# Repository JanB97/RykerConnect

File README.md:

# RykerConnect
Addon Media Display for CanAm Ryker

> [!WARNING]
> Current Hardware Version (REV01) of the MainUnit has a hardware bug.
In my test, I did not connect the reset line of the display to a pin on the esp32. 
I did only connect it to the reset/enable pin of the esp. This seemed to be fine while testing, but with the production boards I am having problems with the initialization.
I would ***NOT*** recommend getting these boards produced right now.
> 
> **Update 05.04.2026**: It's fixed in software for the most part, it seems like it's working now, just a bit buggy on startup (you see weird or old images).
> I have created a Rev2 that uses a gpio as reset line, but this board is not tested, i have not ordered it and you will need to build the firmware yourseld, because you need to change the pinout from using no pin to IO15 for the display reset.

This Project contains a firmware for a esp32s3 that is build on PlattformIO and the Arduino Core, an Android Companion App to get data on the Display and a simple ESP32S3 Board design to fit within a 3D printed case.
I will publish all the projects; however, please keep in mind that I am neither a hardware designer nor a software engineer, so pretty much all of this is messy.
It works, but that is a miracle.
Originally I did intend for this to have many features (e.g., show the weather, maybe map navigation, and more), but my development skills are not good enough right now.

The current features are only:
- Display the current time
- Keep the time while turned off
- Display the current temperature (if Hardware is installed on the board)
- Display current battery percentage of the connected phone
- Display current battery percentage of the connected intercom
- Display 'Spotify' media information
- Display Youtube Music media information
- Display incoming notifications (mostly)
- Display current network status
- ota updated from github or with firmware.bin file.
- Settings for: Brightness, Batteries to show, notification display timeout
- Quick Screen Reset (in case it will still bug out with the newest firmware and only display on one side of the oled)

Things I want to add/fix:
- Notifications are currently mostly working, but sometimes apps do random things and I think the android app needs some work to handle that.

Things to add to REV3 Hardware:
- similar to REV2 extend "empty" space around and under temp sensor, to help it not warm up because of the casing and/or ESP32
- add 3 wire (V, GND, S) connector for external DS18B20 (technically possible with REV1 through the exposed pins

REV3 is most likely (if at all) the next hardware rev i am going to build, as my REV1 is working good enough now, and there is no reason to build rev2 without the external sensor now.

> [!NOTE]
> You will need Programming and Hardware knowlage to get this to work right now, I don't think I can really support this right now, so please ho ahead on your own risk.
> If you can and are willing to help with the board design and programming, feel free to help, I am glad for every help on this!

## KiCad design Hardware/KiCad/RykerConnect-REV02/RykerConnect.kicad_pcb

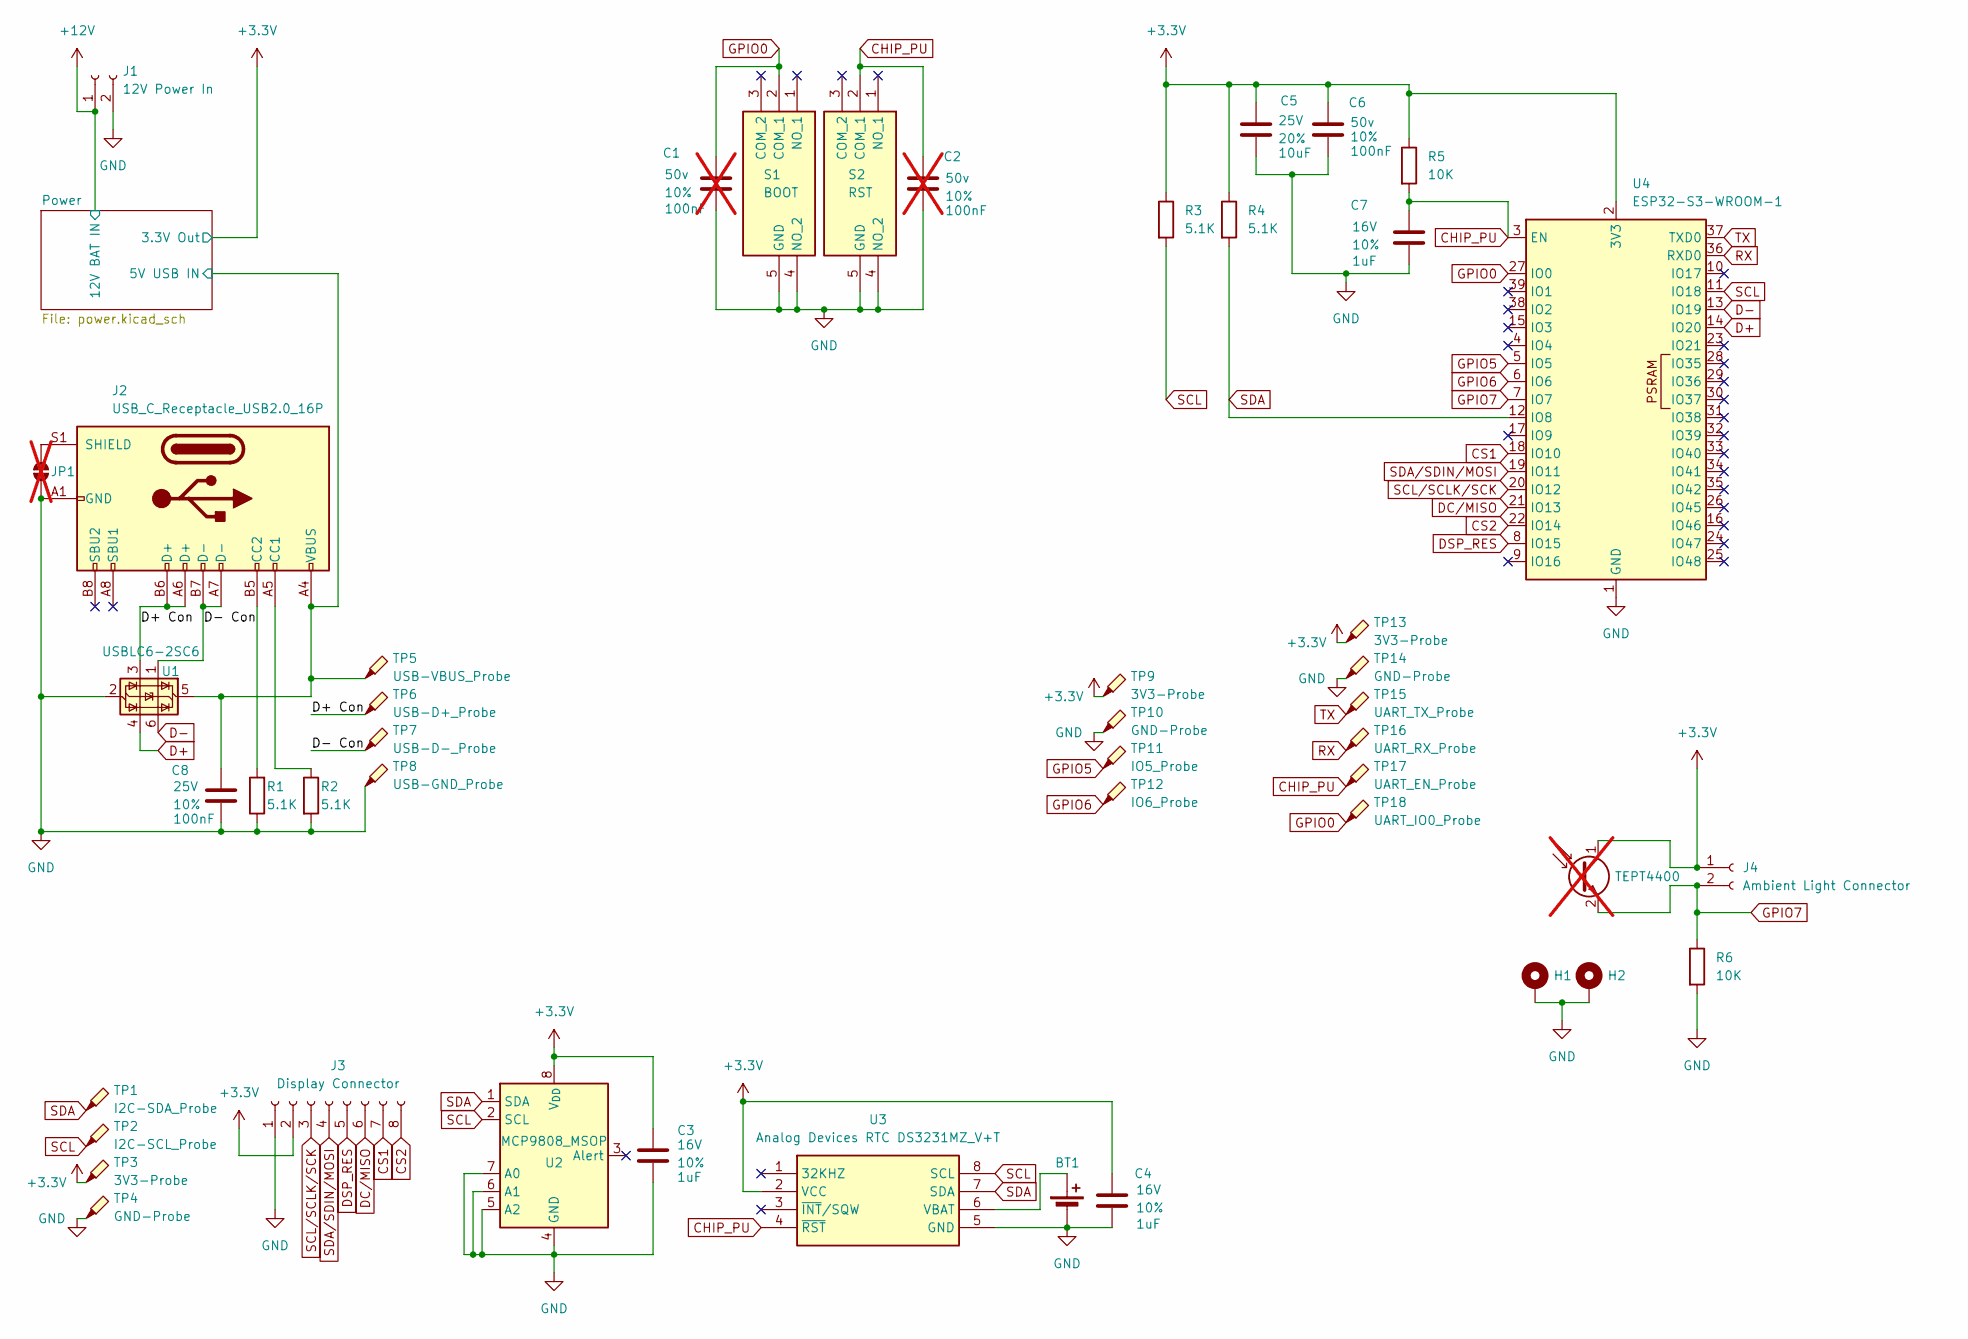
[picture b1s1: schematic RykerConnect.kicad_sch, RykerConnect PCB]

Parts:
BT1: Holders Linx CR2032; BATHLD001
C1, C2: 100nF; C_0603_1608Metric_Pad1.08x0.95mm_HandSolder; Voltage 50v; Tolerance 10%; not fitted
C3, C4, C7: 1uF; C_0603_1608Metric_Pad1.08x0.95mm_HandSolder; Voltage 16V; Tolerance 10%
C5: 10uF; C_0603_1608Metric_Pad1.08x0.95mm_HandSolder; Voltage 25V; Tolerance 20%
C6: 100nF; C_0603_1608Metric_Pad1.08x0.95mm_HandSolder; Voltage 50v; Tolerance 10%
C8: 100nF; C_0603_1608Metric_Pad1.08x0.95mm_HandSolder; Voltage 25V; Tolerance 10%
H1, H2: MountingHole_Pad; MountingHole_2.2mm_M2_ISO14580_Pad_TopBottom
J1: 12V Power In; 43650-02_00,01,02_
J2: USB_C_Receptacle_USB2.0_16P; USB_C_Receptacle_GCT_USB4105-xx-A_16P_TopMnt_Horizontal
J3: Display Connector; JST_SH_SM08B-SRSS-TB_1x08-1MP_P1.00mm_Horizontal
J4: Ambient Light Connector; JST_SH_SM02B-SRSS-TB_1x02-1MP_P1.00mm_Horizontal
JP1: SolderJumper_2_Open; R_0603_1608Metric_Pad0.98x0.95mm_HandSolder; not fitted
Q1: TEPT4400; LED_D3.0mm_Clear; not fitted
R1, R2, R3, R4: 5.1K; R_0805_2012Metric_Pad1.20x1.40mm_HandSolder
R5: 10K; R_0805_2012Metric_Pad1.20x1.40mm_HandSolder; Tolerance 1%
R6: 10K; R_0805_2012Metric_Pad1.20x1.40mm_HandSolder
S1: BOOT; 435451019820; Mouser Part Number 710-435451019820
S2: RST; 435451019820; Mouser Part Number 710-435451019820
TP1: I2C-SDA_Probe; TestPoint_Pad_D2.0mm
TP2: I2C-SCL_Probe; TestPoint_Pad_D2.0mm
TP3, TP9: 3V3-Probe; TestPoint_Pad_D2.0mm
TP4, TP10: GND-Probe; TestPoint_Pad_D2.0mm
TP5: USB-VBUS_Probe; TestPoint_Pad_D1.0mm
TP6: USB-D+_Probe; TestPoint_Pad_D1.0mm
TP7: USB-D-_Probe; TestPoint_Pad_D1.0mm
TP8: USB-GND_Probe; TestPoint_Pad_D1.0mm
TP11: IO5_Probe; TestPoint_Pad_D2.0mm
TP12: IO6_Probe; TestPoint_Pad_D2.0mm
TP13: 3V3-Probe; TestPoint_Pad_D1.5mm
TP14: GND-Probe; TestPoint_Pad_D1.5mm
TP15: UART_TX_Probe; TestPoint_Pad_D1.5mm
TP16: UART_RX_Probe; TestPoint_Pad_D1.5mm
TP17: UART_EN_Probe; TestPoint_Pad_D1.5mm
TP18: UART_IO0_Probe; TestPoint_Pad_D1.5mm
U1: USBLC6-2SC6; SOT-23-6
U2: MCP9808_MSOP; MSOP-8_3x3mm_P0.65mm
U3: Analog Devices RTC DS3231MZ_V+T; SOIC127P600X175-8N; Mouser Part Number 700-DS3231MZ/V+T
U4: ESP32-S3-WROOM-1

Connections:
+3.3V: C3.1, C4.1, C5.1, C6.1, J3.2, J4.1, Q1.1 (C), R3.1, R4.1, R5.1, TP3.1 (1_1), TP9.1 (1_1), TP13.1 (1_1), U2.8 (V_{DD}), U3.2 (VCC), U4.2 (3V3); also elsewhere on the board
+12V: J1.1; also elsewhere on the board
/D+ Con: J2.A6 (D+), J2.B6 (D+), TP6.1 (1_1), U1.3 (I/O2)
/D- Con: J2.A7 (D-), J2.B7 (D-), TP7.1 (1_1), U1.1 (I/O1)
/Power/5V USB IN: C8.1, J2.A4 (VBUS), J2.A9 (VBUS), J2.B4 (VBUS), J2.B9 (VBUS), TP5.1 (1_1), U1.5 (VBUS); also elsewhere on the board
CHIP_PU: C2.1, C7.1, R5.2, S2.2 (COM_1), TP17.1 (1_1), U3.4 (~RST), U4.3 (EN)
CS1: J3.7, U4.18 (IO10)
CS2: J3.8, U4.22 (IO14)
D+: U1.4 (I/O2), U4.14 (IO20)
D-: U1.6 (I/O1), U4.13 (IO19)
DC/MISO: J3.6, U4.21 (IO13)
DSP_RES: J3.5, U4.8 (IO15)
GND: BT1.2 (-), C1.2, C2.2, C3.2, C4.2, C5.2, C6.2, C7.2, C8.2, H1.1 (1_1), H2.1 (1_1), J1.2, J2.A1 (GND), J2.A12 (GND), J2.B1 (GND), J2.B12 (GND), J3.1, JP1.1 (A), R1.1, R2.2, R6.2, S1.4 (NO_2), S1.5 (GND), S2.4 (NO_2), S2.5 (GND), TP4.1 (1_1), TP8.1 (1_1), TP10.1 (1_1), TP14.1 (1_1), U1.2 (GND), U2.4 (GND), U2.5 (A2), U2.6 (A1), U2.7 (A0), U3.5 (GND), U4.1 (GND), U4.40 (GND), U4.41 (GND); also elsewhere on the board
GPIO0: C1.1, S1.2 (COM_1), TP18.1 (1_1), U4.27 (IO0)
GPIO5: TP11.1 (1_1), U4.5 (IO5)
GPIO6: TP12.1 (1_1), U4.6 (IO6)
GPIO7: J4.2, Q1.2 (E), R6.1, U4.7 (IO7)
unnamed: BT1.1 (+), U3.6 (VBAT)
unnamed: J2.A5 (CC1), R2.1
unnamed: J2.B5 (CC2), R1.2
unnamed: J2.S1 (SHIELD), JP1.2 (B)
RX: TP16.1 (1_1), U4.36 (RXD0)
SCL: R3.2, TP2.1 (1_1), U2.2 (SCL), U3.8 (SCL), U4.11 (IO18)
SCL/SCLK/SCK: J3.3, U4.20 (IO12)
SDA: R4.2, TP1.1 (1_1), U2.1 (SDA), U3.7 (SDA), U4.12 (IO8)
SDA/SDIN/MOSI: J3.4, U4.19 (IO11)
TX: TP15.1 (1_1), U4.37 (TXD0)

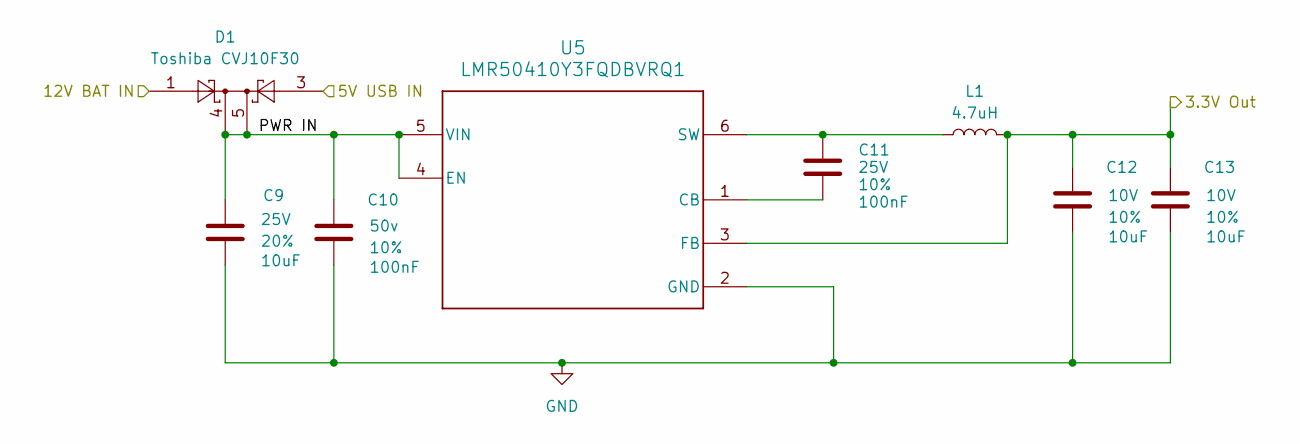
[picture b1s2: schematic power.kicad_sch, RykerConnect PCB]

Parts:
C9: 10uF; C_0603_1608Metric_Pad1.08x0.95mm_HandSolder; Voltage 25V; Tolerance 20%
C10: 100nF; C_0603_1608Metric_Pad1.08x0.95mm_HandSolder; Voltage 50v; Tolerance 10%
C11: 100nF; C_0603_1608Metric_Pad1.08x0.95mm_HandSolder; Voltage 25V; Tolerance 10%
C12, C13: 10uF; C_0805_2012Metric_Pad1.18x1.45mm_HandSolder; Voltage 10V; Tolerance 10%
D1: Toshiba CVJ10F30; SOTFL65P210X75-5N
L1: 4.7uH; INDPM5653X430N
U5: LMR50410Y3FQDBVRQ1; DBV0006A-IPC_A

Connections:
+3.3V: C12.1, C13.1, L1.2, U5.3 (FB); also elsewhere on the board
+12V: D1.1; also elsewhere on the board
/Power/5V USB IN: D1.3; also elsewhere on the board
/Power/PWR IN: C9.1, C10.1, D1.4, D1.5, U5.4 (EN), U5.5 (VIN)
GND: C9.2, C10.2, C12.2, C13.2, U5.2 (GND); also elsewhere on the board
unnamed: C11.2, U5.1 (CB)
unnamed: C11.1, L1.1, U5.6 (SW)

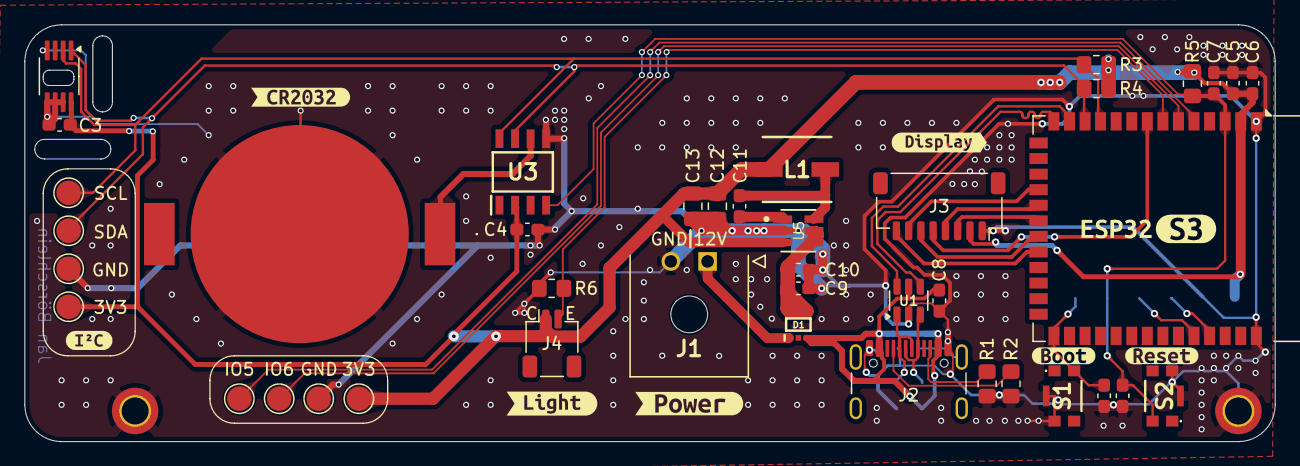
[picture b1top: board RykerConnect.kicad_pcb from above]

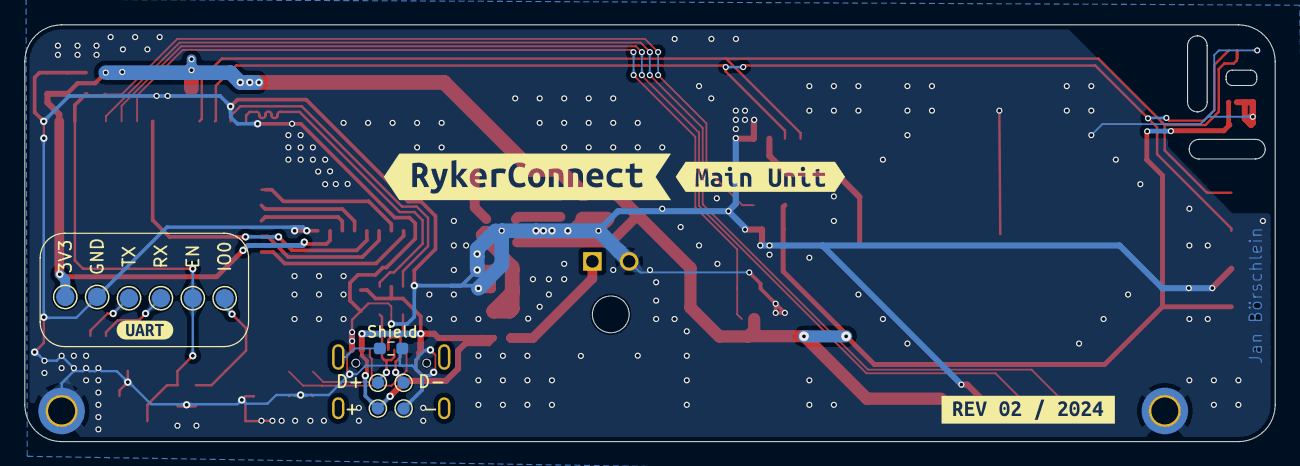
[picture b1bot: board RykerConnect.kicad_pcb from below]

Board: 2 copper layers, 102.0 x 34.0 mm, 67 parts (16 on the bottom side), 30 nets.

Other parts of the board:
kibuzzard-6647CFBD: G***; kibuzzard-6647CFBD
kibuzzard-66281C1F: G***; kibuzzard-66281C1F
kibuzzard-66281DA5: G***; kibuzzard-66281DA5
kibuzzard-66281FA1: G***; kibuzzard-66281FA1
kibuzzard-66282B71: G***; kibuzzard-66282B71
kibuzzard-66296C5A: G***; kibuzzard-66296C5A
kibuzzard-662805BB: G***; kibuzzard-662805BB
kibuzzard-662805C3: G***; kibuzzard-662805C3
kibuzzard-6628061E: G***; kibuzzard-6628061E
kibuzzard-6628064B: G***; kibuzzard-6628064B
kibuzzard-6628065E: G***; kibuzzard-6628065E
kibuzzard-66280634: G***; kibuzzard-66280634
kibuzzard-66281340: G***; kibuzzard-66281340

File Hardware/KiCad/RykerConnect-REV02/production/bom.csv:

Designator,Footprint,Quantity,Value,LCSC Part #
BT1,BATHLD001,1,Battery_Cell,
"C10, C11, C6, C8",0603,4,100nF,
"C12, C13",0805,2,10uF,
"C3, C4, C7",0603,3,1uF,
"C5, C9",0603,2,10uF,
D1,SOTFL65P210X75-5N,1,Toshiba CVJ10F30,
J1,"43650-02_00,01,02_",1,12V Power In,
J2,USB_C_Receptacle_GCT_USB4105-xx-A_16P_TopMnt_Horizontal,1,USB_C_Receptacle_USB2.0_16P,
J3,JST_SH_SM08B-SRSS-TB_1x08-1MP_P1.00mm_Horizontal,1,Display Connector,
J4,JST_SH_SM02B-SRSS-TB_1x02-1MP_P1.00mm_Horizontal,1,Ambient Light Connector,
L1,INDPM5653X430N,1,L,
"R1, R2, R3, R4",0805,4,5.1K,
"R5, R6",0805,2,10K,
S1,435451019820,1,BOOT,
S2,435451019820,1,RST,
TP1,TestPoint_Pad_D2.0mm,1,I2C-SDA_Probe,
"TP10, TP4",TestPoint_Pad_D2.0mm,2,GND-Probe,
TP11,TestPoint_Pad_D2.0mm,1,IO5_Probe,
TP12,TestPoint_Pad_D2.0mm,1,IO6_Probe,
TP13,TestPoint_Pad_D1.5mm,1,3V3-Probe,
TP14,TestPoint_Pad_D1.5mm,1,GND-Probe,
TP15,TestPoint_Pad_D1.5mm,1,UART_TX_Probe,
TP16,TestPoint_Pad_D1.5mm,1,UART_RX_Probe,
TP17,TestPoint_Pad_D1.5mm,1,UART_EN_Probe,
TP18,TestPoint_Pad_D1.5mm,1,UART_IO0_Probe,
TP2,TestPoint_Pad_D2.0mm,1,I2C-SCL_Probe,
"TP3, TP9",TestPoint_Pad_D2.0mm,2,3V3-Probe,
TP5,TestPoint_Pad_D1.0mm,1,USB-VBUS_Probe,
TP6,TestPoint_Pad_D1.0mm,1,USB-D+_Probe,
TP7,TestPoint_Pad_D1.0mm,1,USB-D-_Probe,
TP8,TestPoint_Pad_D1.0mm,1,USB-GND_Probe,
U1,SOT-23-6,1,USBLC6-2SC6,
U2,MSOP-8_3x3mm_P0.65mm,1,MCP9808_MSOP,
U3,SOIC127P600X175-8N,1,Analog Devices RTC DS3231MZ_V+T,
U4,ESP32-S3-WROOM-1,1,ESP32-S3-WROOM-1,
U5,DBV0006A-IPC_A,1,LMR50410Y3FQDBVRQ1,

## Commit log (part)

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2024-11-24 Initial Upload
    Initial Upload, REV01 has a HARDWARE Bug! - Not recommended.
2024-11-25 Updated libraries
    Updated libraries and generate firmware v0001.
2025-04-21 add youtube music add 5g listener add intercombattery some fixes
2025-04-21 optimize youtube music + release build
2026-04-03 Firmware V2
    Firmware V2!
2026-04-03 Update firmware version tag and remove debug
2026-04-03 fix firnware downloading https!
2026-04-03 Update Firmware and APK
    Add Features to Apk to utilize functions already implemented in firmware.
    Stability improvments to firmware and app.
    Add "automatic" firmware updater, to download update from github.
2026-04-03 update buttons hiding
2026-04-03 update vor animation rework
2026-04-03 animation update!
2026-04-03 Remove 1 second offset, because with new firmware it is instant.
2026-04-03 permission checks and onboarding
2026-04-03 persmission checks & onboarding
2026-04-03 releases
2026-04-03 rename of firmware versions + fix to pairing code display and screen initialization
2026-04-04 firmware repair
    Aus irgendeinem Grund war sie defekt (auch etwas zu klein)
2026-04-04 display init fix - remove second begin()
2026-04-04 fix pairing displayed even if bond is there.
2026-04-04 see changes of firmware bin v00.03
2026-04-04 init fixes from main
2026-04-04 exclude keystore
    update gitignore to exclude apk keystore
2026-04-04 move prerelease apks
2026-04-04 add 1.0 apk and changelog file
2026-04-04 remove old files
2026-04-04 add firmware v0.4
2026-04-04 update android app source code
    Update app to v1, add settings to support linux development
2026-04-04 source update for firmware v0.4
2026-04-04 fix wifi credentials fields and states
2026-04-05 fix ble hostname not beeing advertised, updated version number
2026-04-05 Revise README with hardware bug update and features
    Updated warning about hardware bug and added details on firmware fixes and future improvements.
2026-04-05 update pcb to schematics
2026-04-06 add volume and hardware version ble functions, low battery warnings, implement auto brightness, ble timeout
2026-04-06 update rev 2
2026-04-06 misc
2026-04-06 remove non minified builds
2026-04-06 add new version 1.3, change names of old versions, add new version to changelog
2026-04-06 source for firmware 00.06, see changelog for changes
2026-04-06 source code for app version 1.3.0, see changelog for changes
2026-04-06 add new firmware version 00.06 and changelog
2026-04-07 Revert OTA download logic to V00.05
2026-04-07 increase version number, increase serial speed, add new firmware.bin
2026-04-07 add debug fps counter
2026-04-07 dimm test, flickering....
2026-04-09 bluetooth stability improvements, bump app to 1.3.1
